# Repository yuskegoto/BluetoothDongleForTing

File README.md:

# Bluetooth Dongle for Ting
This is an attempt to give bluetooth HID ability to the OiD reading pens. I named this repo as "dongle", however the device is quite big, as you won't call it dongle. Well, who cares!

## Generating OiD
I used the OiD generator called (Tingeltangel.)[https://github.com/Martin-Dames/Tingeltangel]
Java binary can be also found (here)[https://www.ting-el-tangel.de/doku.php?id=download] Please be aware that most of the information is avaiable only on German. However the app is straight forward, probably you can use it without much knowledge about German.

## System
As shown here, a letter is modulated to simple sound pulse like morse signal based on ascii code binary bits. The processor (ATTiny45) samples the sound burst and encodes the sampled bits based on simple packet format with header and footer.

The sound files are stored to the Ting device as wav or MP3. When user reads a OiD printed surface with the pen, Ting plays the corresponding sound file.

The daata is extracted using footer and header. No parity bit is used. Just simple (and primitive) bit alignment.

## Circuit
The circit is extremely simple, using only one OP amp and an ATTiny controller.

## Reference
There is also a thread about Ting reverse engineering in mikrocontroller.net. The thread is also in German too.
(https://www.mikrocontroller.net/topic/214479)[https://www.mikrocontroller.net/topic/214479]

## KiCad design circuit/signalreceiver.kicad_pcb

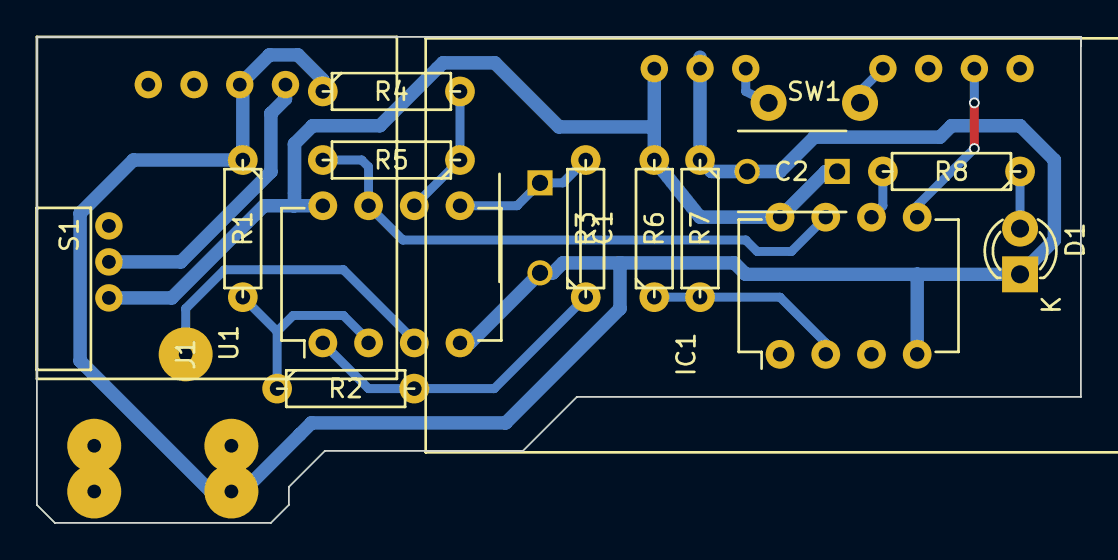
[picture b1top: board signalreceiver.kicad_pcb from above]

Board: 2 copper layers, 58.0 x 27.0 mm, 18 parts (0 on the bottom side), 15 nets.

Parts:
C1: 22nF; C_Disc_D6_P5
C2: 100nF; C_Disc_D6_P5
D1: LED; LED-3MM
IC1: ATTINY45-P; DIP-8_W7.62mm
J1: JACK_TRS_4PINS; Audio_Klinke
R1, R2, R5, R7: 10k; R3-LARGE_PADS
R3: 4,7k; R3-LARGE_PADS
R4: 1k; R3-LARGE_PADS
R6: 33k; R3-LARGE_PADS
R8: 100; R3-LARGE_PADS
S1: PW_SW
SW1: PAIRING; PUSH_SW
U1: LM358N; DIP-8_W7.62mm
U2: LipoCharger; LiPoCharger
U3: BT_Tastatur; Bluefruit_EZ-KEY_HID

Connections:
/BAT_LEVEL: IC1.2, R6.1, R7.2
/KB_RX: IC1.5, U3.2
/LED: IC1.6, R8.2
GND: C1.2, C2.2, D1.1, IC1.4, J1.1, R1.1, R4.1, R7.1, U1.4, U2.3, U3.8
unnamed: C1.1, R3.2, U1.5
unnamed: D1.2, R8.1
unnamed: IC1.7, R5.2, U1.7
unnamed: J1.2, U1.3
unnamed: R1.2, R2.1, U1.2
unnamed: R2.2, R3.1, U1.1
unnamed: R4.2, R5.1, U1.6
unnamed: S1.2, U2.4
unnamed: SW1.1, U3.7
unnamed: SW1.2, U3.4
VCC: C2.1, IC1.8, R6.2, S1.1, U1.8, U3.9

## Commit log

2018-11-11 commit for publish
2018-11-11 cleaned up cache files
2021-05-25 Added some content for readme.
